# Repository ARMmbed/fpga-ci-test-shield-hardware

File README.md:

# FPGA CI Test shield - hardware design

Note: the RTL code for the FPGA lives in a separate repository: https://github.com/ARMmbed/fpga-ci-test-shield

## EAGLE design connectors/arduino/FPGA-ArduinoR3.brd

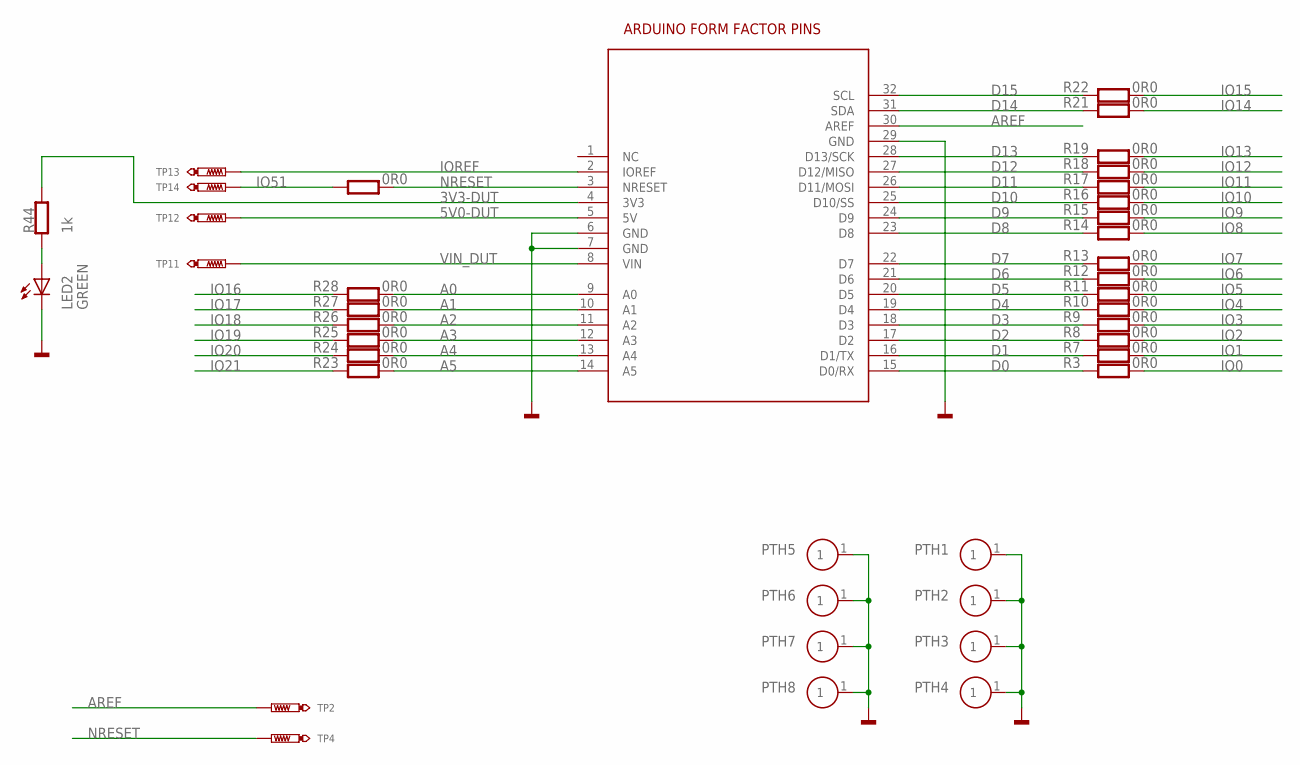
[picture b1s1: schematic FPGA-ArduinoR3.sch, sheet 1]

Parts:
BRD1: ARDUINO-R3_SILK; ARDUINO-R3-SILK
LED2: GREEN; CHIPLED_0603
PTH1, PTH2, PTH3, PTH4, PTH5, PTH6, PTH7, PTH8: FIXINGHOLE; PTH-140-300
R2, R3, R7, R8, R9, R10, R11, R12, R13, R14, R15, R16, R17, R18, R19, R21, R22, R23, R24, R25, R26, R27, R28: 0R0; 0603
R44: 1k; 0603
TP2, TP4, TP11, TP12, TP13, TP14: TEST_POINT-50R-SMD; TP50-SMD

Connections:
3V3-DUT: BRD1.4 (3V3), R44.2
5V0-DUT: BRD1.5 (5V), TP12.TP
A0: BRD1.9 (A0), R28.1
A1: BRD1.10 (A1), R27.1
A2: BRD1.11 (A2), R26.1
A3: BRD1.12 (A3), R25.1
A4: BRD1.13 (A4), R24.1
A5: BRD1.14 (A5), R23.1
AREF: BRD1.30 (AREF), TP2.TP
D0: BRD1.15 (D0/RX), R3.2
D1: BRD1.16 (D1/TX), R7.2
D2: BRD1.17 (D2), R8.2
D3: BRD1.18 (D3), R9.2
D4: BRD1.19 (D4), R10.2
D5: BRD1.20 (D5), R11.2
D6: BRD1.21 (D6), R12.2
D7: BRD1.22 (D7), R13.2
D8: BRD1.23 (D8), R14.2
D9: BRD1.24 (D9), R15.2
D10: BRD1.25 (D10/SS), R16.2
D11: BRD1.26 (D11/MOSI), R17.2
D12: BRD1.27 (D12/MISO), R18.2
D13: BRD1.28 (D13/SCK), R19.2
D14: BRD1.31 (SDA), R21.2
D15: BRD1.32 (SCL), R22.2
GND: BRD1.6 (GND), BRD1.7 (GND), BRD1.29 (GND), LED2.C, PTH1.1, PTH2.1, PTH3.1, PTH4.1, PTH5.1, PTH6.1, PTH7.1, PTH8.1; also elsewhere on the board
IO0: R3.1; also elsewhere on the board
IO1: R7.1; also elsewhere on the board
IO2: R8.1; also elsewhere on the board
IO3: R9.1; also elsewhere on the board
IO4: R10.1; also elsewhere on the board
IO5: R11.1; also elsewhere on the board
IO6: R12.1; also elsewhere on the board
IO7: R13.1; also elsewhere on the board
IO8: R14.1; also elsewhere on the board
IO9: R15.1; also elsewhere on the board
IO10: R16.1; also elsewhere on the board
IO11: R17.1; also elsewhere on the board
IO12: R18.1; also elsewhere on the board
IO13: R19.1; also elsewhere on the board
IO14: R21.1; also elsewhere on the board
IO15: R22.1; also elsewhere on the board
IO16: R28.2; also elsewhere on the board
IO17: R27.2; also elsewhere on the board
IO18: R26.2; also elsewhere on the board
IO19: R25.2; also elsewhere on the board
IO20: R24.2; also elsewhere on the board
IO21: R23.2; also elsewhere on the board
IO51: R2.2, TP14.TP; also elsewhere on the board
IOREF: BRD1.2 (IOREF), TP13.TP
unnamed: LED2.A, R44.1
NRESET: BRD1.3 (NRESET), R2.1, TP4.TP
VIN_DUT: BRD1.8 (VIN), TP11.TP

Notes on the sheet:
ARDUINO FORM FACTOR PINS

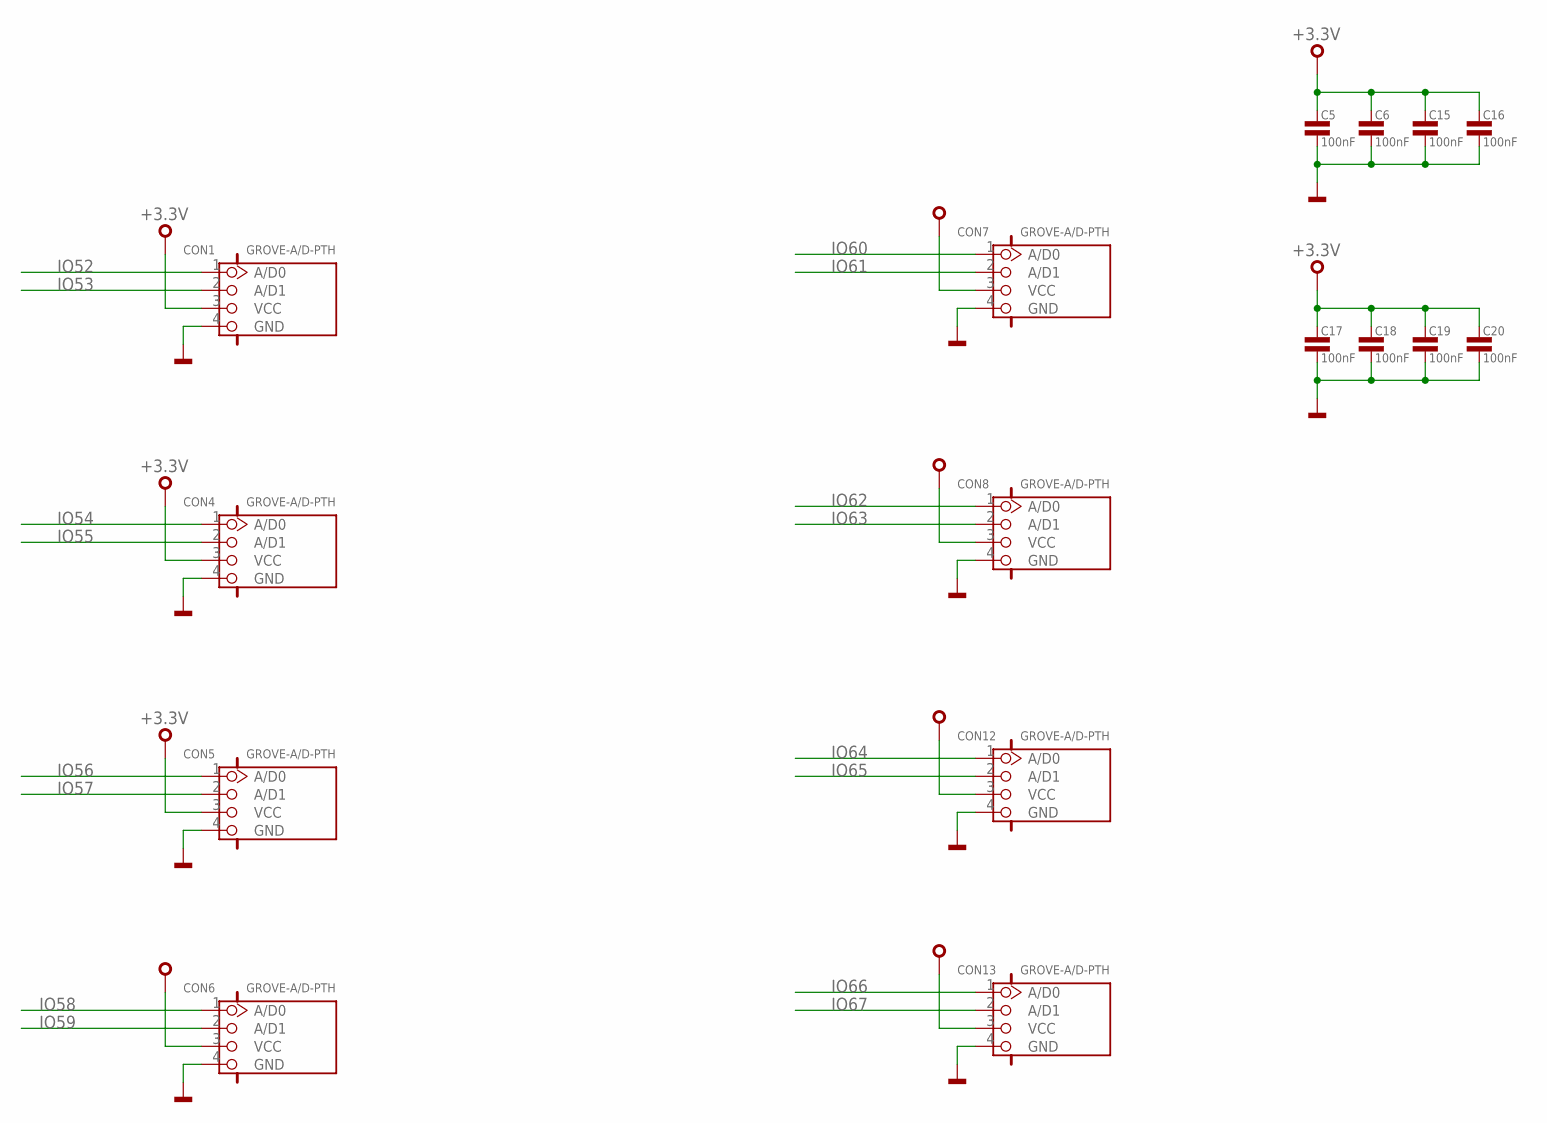
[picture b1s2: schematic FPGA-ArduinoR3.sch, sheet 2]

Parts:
C5, C6, C15, C16, C17, C18, C19, C20: 100nF; 0603
CON1, CON4, CON5, CON6, CON7, CON8, CON12, CON13: GROVE-A/D-PTH; HW4-2.0

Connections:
+3.3V: C5.1, C6.1, C15.1, C16.1, C17.1, C18.1, C19.1, C20.1, CON1.3 (VCC), CON4.3 (VCC), CON5.3 (VCC), CON6.3 (VCC), CON7.3 (VCC), CON8.3 (VCC), CON12.3 (VCC), CON13.3 (VCC); also elsewhere on the board
GND: C5.2, C6.2, C15.2, C16.2, C17.2, C18.2, C19.2, C20.2, CON1.4 (GND), CON4.4 (GND), CON5.4 (GND), CON6.4 (GND), CON7.4 (GND), CON8.4 (GND), CON12.4 (GND), CON13.4 (GND); also elsewhere on the board
IO52: CON1.1 (A/D0); also elsewhere on the board
IO53: CON1.2 (A/D1); also elsewhere on the board
IO54: CON4.1 (A/D0); also elsewhere on the board
IO55: CON4.2 (A/D1); also elsewhere on the board
IO56: CON5.1 (A/D0); also elsewhere on the board
IO57: CON5.2 (A/D1); also elsewhere on the board
IO58: CON6.1 (A/D0); also elsewhere on the board
IO59: CON6.2 (A/D1); also elsewhere on the board
IO60: CON7.1 (A/D0); also elsewhere on the board
IO61: CON7.2 (A/D1); also elsewhere on the board
IO62: CON8.1 (A/D0); also elsewhere on the board
IO63: CON8.2 (A/D1); also elsewhere on the board
IO64: CON12.1 (A/D0); also elsewhere on the board
IO65: CON12.2 (A/D1); also elsewhere on the board
IO66: CON13.1 (A/D0); also elsewhere on the board
IO67: CON13.2 (A/D1); also elsewhere on the board

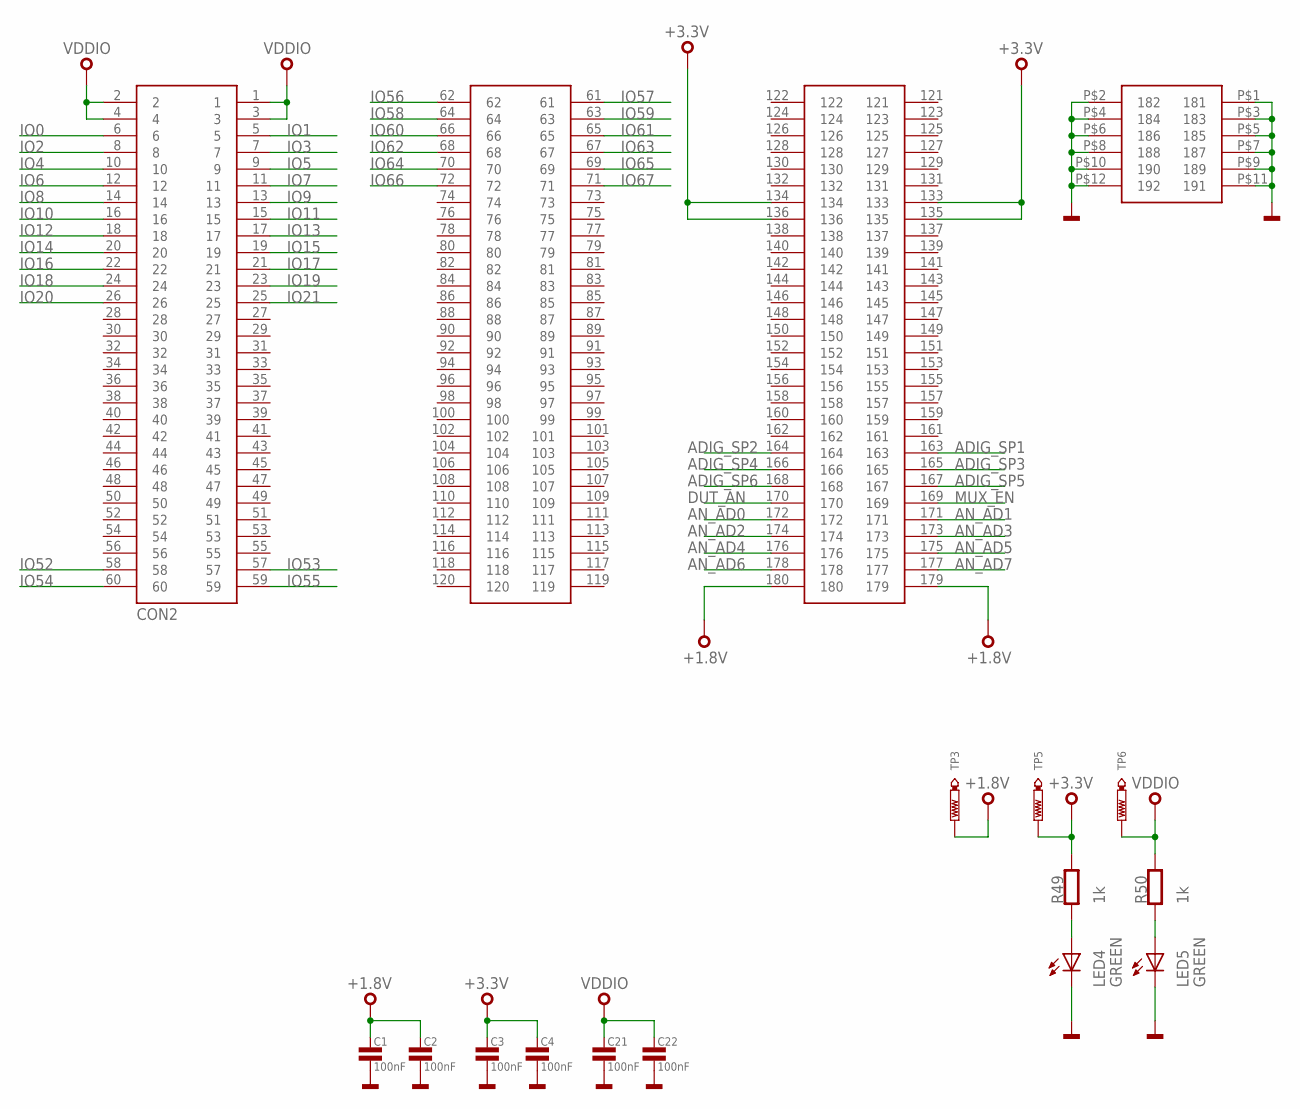
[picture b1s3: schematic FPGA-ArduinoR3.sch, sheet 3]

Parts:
C1, C2, C3, C4, C21, C22: 100nF; 0603
CON2: QSH-090-01-L-D-A
LED4, LED5: GREEN; CHIPLED_0603
R49, R50: 1k; 0603
TP3, TP5, TP6: TEST_POINT-50R-PTH; TP50-PTH

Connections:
+1.8V: C1.1, C2.1, CON2.179, CON2.180, TP3.TP; also elsewhere on the board
+3.3V: C3.1, C4.1, CON2.133, CON2.134, CON2.135, CON2.136, R49.2, TP5.TP; also elsewhere on the board
ADIG_SP1: CON2.163
ADIG_SP2: CON2.164
ADIG_SP3: CON2.165
ADIG_SP4: CON2.166
ADIG_SP5: CON2.167
ADIG_SP6: CON2.168
AN_AD0: CON2.172; also elsewhere on the board
AN_AD1: CON2.171; also elsewhere on the board
AN_AD2: CON2.174; also elsewhere on the board
AN_AD3: CON2.173; also elsewhere on the board
AN_AD4: CON2.176; also elsewhere on the board
AN_AD5: CON2.175; also elsewhere on the board
AN_AD6: CON2.178; also elsewhere on the board
AN_AD7: CON2.177; also elsewhere on the board
DUT_AN: CON2.170; also elsewhere on the board
GND: C1.2, C2.2, C3.2, C4.2, C21.2, C22.2, CON2.P$1 (181), CON2.P$2 (182), CON2.P$3 (183), CON2.P$4 (184), CON2.P$5 (185), CON2.P$6 (186), CON2.P$7 (187), CON2.P$8 (188), CON2.P$9 (189), CON2.P$10 (190), CON2.P$11 (191), CON2.P$12 (192), LED4.C, LED5.C; also elsewhere on the board
IO0: CON2.6; also elsewhere on the board
IO1: CON2.5; also elsewhere on the board
IO2: CON2.8; also elsewhere on the board
IO3: CON2.7; also elsewhere on the board
IO4: CON2.10; also elsewhere on the board
IO5: CON2.9; also elsewhere on the board
IO6: CON2.12; also elsewhere on the board
IO7: CON2.11; also elsewhere on the board
IO8: CON2.14; also elsewhere on the board
IO9: CON2.13; also elsewhere on the board
IO10: CON2.16; also elsewhere on the board
IO11: CON2.15; also elsewhere on the board
IO12: CON2.18; also elsewhere on the board
IO13: CON2.17; also elsewhere on the board
IO14: CON2.20; also elsewhere on the board
IO15: CON2.19; also elsewhere on the board
IO16: CON2.22; also elsewhere on the board
IO17: CON2.21; also elsewhere on the board
IO18: CON2.24; also elsewhere on the board
IO19: CON2.23; also elsewhere on the board
IO20: CON2.26; also elsewhere on the board
IO21: CON2.25; also elsewhere on the board
IO52: CON2.58; also elsewhere on the board
IO53: CON2.57; also elsewhere on the board
IO54: CON2.60; also elsewhere on the board
IO55: CON2.59; also elsewhere on the board
IO56: CON2.62; also elsewhere on the board
IO57: CON2.61; also elsewhere on the board
IO58: CON2.64; also elsewhere on the board
IO59: CON2.63; also elsewhere on the board
IO60: CON2.66; also elsewhere on the board
IO61: CON2.65; also elsewhere on the board
IO62: CON2.68; also elsewhere on the board
IO63: CON2.67; also elsewhere on the board
IO64: CON2.70; also elsewhere on the board
IO65: CON2.69; also elsewhere on the board
IO66: CON2.72; also elsewhere on the board
IO67: CON2.71; also elsewhere on the board
MUX_EN: CON2.169; also elsewhere on the board
unnamed: LED4.A, R49.1
unnamed: LED5.A, R50.1
VDDIO: C21.1, C22.1, CON2.1, CON2.2, CON2.3, CON2.4, R50.2, TP6.TP; also elsewhere on the board

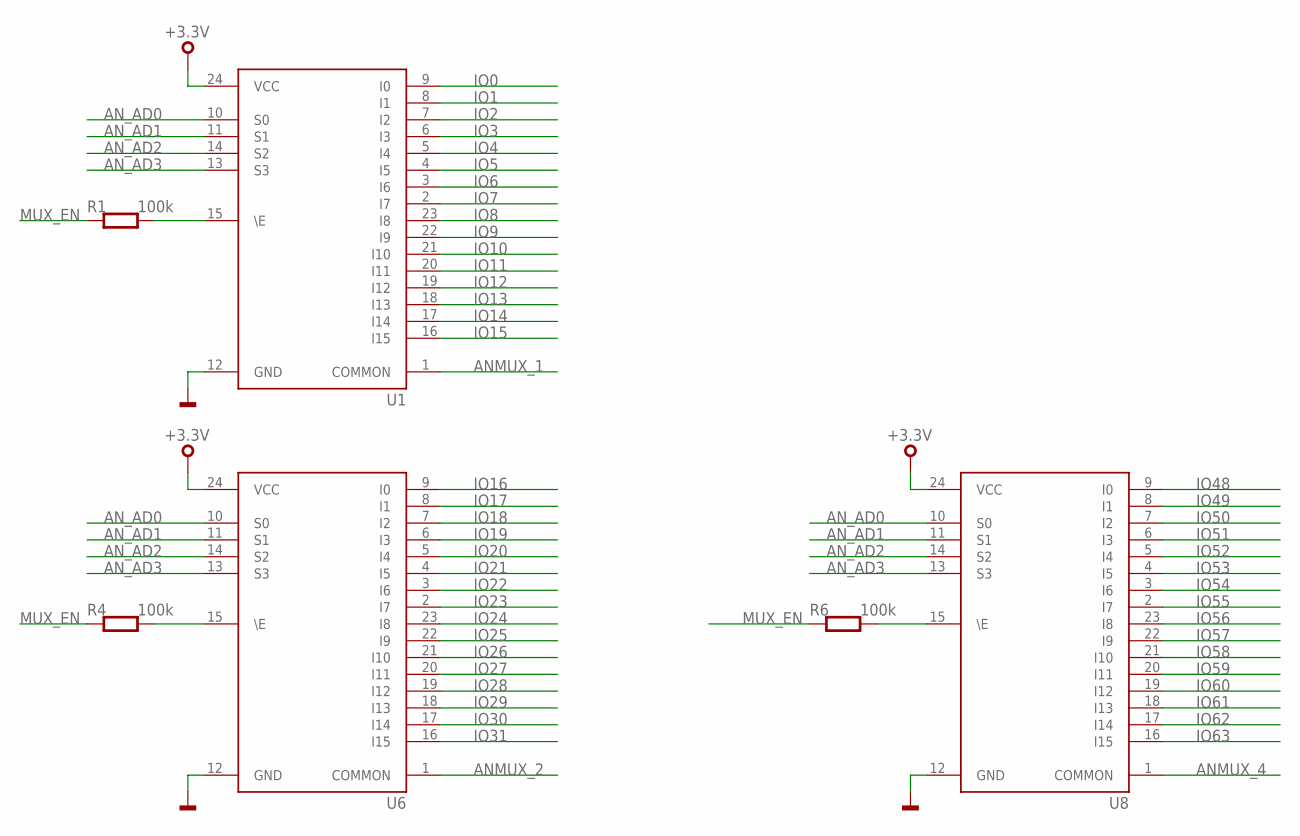
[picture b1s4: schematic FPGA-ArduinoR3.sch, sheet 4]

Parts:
R1, R4, R6: 100k; 0603
U1, U6, U8: CD74HCT4067; SO24

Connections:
+3.3V: U1.24 (VCC), U6.24 (VCC), U8.24 (VCC); also elsewhere on the board
ANMUX_1: U1.1 (COMMON); also elsewhere on the board
ANMUX_2: U6.1 (COMMON); also elsewhere on the board
ANMUX_4: U8.1 (COMMON); also elsewhere on the board
AN_AD0: U1.10 (S0), U6.10 (S0), U8.10 (S0); also elsewhere on the board
AN_AD1: U1.11 (S1), U6.11 (S1), U8.11 (S1); also elsewhere on the board
AN_AD2: U1.14 (S2), U6.14 (S2), U8.14 (S2); also elsewhere on the board
AN_AD3: U1.13 (S3), U6.13 (S3), U8.13 (S3); also elsewhere on the board
GND: U1.12 (GND), U6.12 (GND), U8.12 (GND); also elsewhere on the board
IO0: U1.9 (I0); also elsewhere on the board
IO1: U1.8 (I1); also elsewhere on the board
IO2: U1.7 (I2); also elsewhere on the board
IO3: U1.6 (I3); also elsewhere on the board
IO4: U1.5 (I4); also elsewhere on the board
IO5: U1.4 (I5); also elsewhere on the board
IO6: U1.3 (I6); also elsewhere on the board
IO7: U1.2 (I7); also elsewhere on the board
IO8: U1.23 (I8); also elsewhere on the board
IO9: U1.22 (I9); also elsewhere on the board
IO10: U1.21 (I10); also elsewhere on the board
IO11: U1.20 (I11); also elsewhere on the board
IO12: U1.19 (I12); also elsewhere on the board
IO13: U1.18 (I13); also elsewhere on the board
IO14: U1.17 (I14); also elsewhere on the board
IO15: U1.16 (I15); also elsewhere on the board
IO16: U6.9 (I0); also elsewhere on the board
IO17: U6.8 (I1); also elsewhere on the board
IO18: U6.7 (I2); also elsewhere on the board
IO19: U6.6 (I3); also elsewhere on the board
IO20: U6.5 (I4); also elsewhere on the board
IO21: U6.4 (I5); also elsewhere on the board
IO22: U6.3 (I6)
IO23: U6.2 (I7)
IO24: U6.23 (I8)
IO25: U6.22 (I9)
IO26: U6.21 (I10)
IO27: U6.20 (I11)
IO28: U6.19 (I12)
IO29: U6.18 (I13)
IO30: U6.17 (I14)
IO31: U6.16 (I15)
IO48: U8.9 (I0)
IO49: U8.8 (I1)
IO50: U8.7 (I2)
IO51: U8.6 (I3); also elsewhere on the board
IO52: U8.5 (I4); also elsewhere on the board
IO53: U8.4 (I5); also elsewhere on the board
IO54: U8.3 (I6); also elsewhere on the board
IO55: U8.2 (I7); also elsewhere on the board
IO56: U8.23 (I8); also elsewhere on the board
IO57: U8.22 (I9); also elsewhere on the board
IO58: U8.21 (I10); also elsewhere on the board
IO59: U8.20 (I11); also elsewhere on the board
IO60: U8.19 (I12); also elsewhere on the board
IO61: U8.18 (I13); also elsewhere on the board
IO62: U8.17 (I14); also elsewhere on the board
IO63: U8.16 (I15); also elsewhere on the board
MUX_EN: R1.1, R4.1, R6.1; also elsewhere on the board
unnamed: R4.2, U6.15 (\E)
unnamed: R1.2, U1.15 (\E)
unnamed: R6.2, U8.15 (\E)

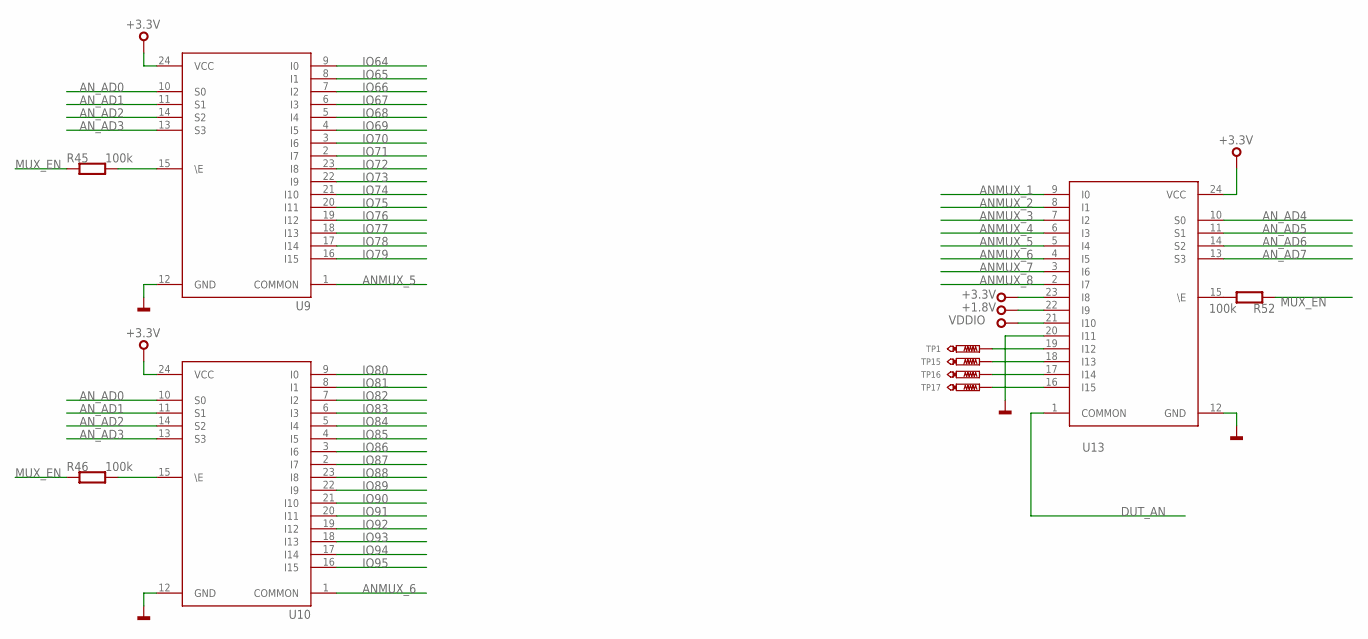
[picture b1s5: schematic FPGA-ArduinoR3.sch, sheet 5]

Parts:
R45, R46, R52: 100k; 0603
TP1, TP15, TP16, TP17: TEST_POINT-50R-PTH; TP50-PTH
U9, U10, U13: CD74HCT4067; SO24

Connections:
+1.8V: U13.22 (I9); also elsewhere on the board
+3.3V: U9.24 (VCC), U10.24 (VCC), U13.23 (I8), U13.24 (VCC); also elsewhere on the board
ANMUX_1: U13.9 (I0); also elsewhere on the board
ANMUX_2: U13.8 (I1); also elsewhere on the board
ANMUX_3: U13.7 (I2)
ANMUX_4: U13.6 (I3); also elsewhere on the board
ANMUX_5: U9.1 (COMMON), U13.5 (I4)
ANMUX_6: U10.1 (COMMON), U13.4 (I5)
ANMUX_7: U13.3 (I6)
ANMUX_8: U13.2 (I7)
AN_AD0: U9.10 (S0), U10.10 (S0); also elsewhere on the board
AN_AD1: U9.11 (S1), U10.11 (S1); also elsewhere on the board
AN_AD2: U9.14 (S2), U10.14 (S2); also elsewhere on the board
AN_AD3: U9.13 (S3), U10.13 (S3); also elsewhere on the board
AN_AD4: U13.10 (S0); also elsewhere on the board
AN_AD5: U13.11 (S1); also elsewhere on the board
AN_AD6: U13.14 (S2); also elsewhere on the board
AN_AD7: U13.13 (S3); also elsewhere on the board
DUT_AN: U13.1 (COMMON); also elsewhere on the board
GND: U9.12 (GND), U10.12 (GND), U13.12 (GND), U13.20 (I11); also elsewhere on the board
IO64: U9.9 (I0); also elsewhere on the board
IO65: U9.8 (I1); also elsewhere on the board
IO66: U9.7 (I2); also elsewhere on the board
IO67: U9.6 (I3); also elsewhere on the board
IO68: U9.5 (I4)
IO69: U9.4 (I5)
IO70: U9.3 (I6)
IO71: U9.2 (I7)
IO72: U9.23 (I8)
IO73: U9.22 (I9)
IO74: U9.21 (I10)
IO75: U9.20 (I11)
IO76: U9.19 (I12)
IO77: U9.18 (I13)
IO78: U9.17 (I14)
IO79: U9.16 (I15)
IO80: U10.9 (I0)
IO81: U10.8 (I1)
IO82: U10.7 (I2)
IO83: U10.6 (I3)
IO84: U10.5 (I4)
IO85: U10.4 (I5)
IO86: U10.3 (I6)
IO87: U10.2 (I7)
IO88: U10.23 (I8)
IO89: U10.22 (I9)
IO90: U10.21 (I10)
IO91: U10.20 (I11)
IO92: U10.19 (I12)
IO93: U10.18 (I13)
IO94: U10.17 (I14)
IO95: U10.16 (I15)
MUX_EN: R45.1, R46.1, R52.1; also elsewhere on the board
unnamed: R45.2, U9.15 (\E)
unnamed: R46.2, U10.15 (\E)
unnamed: R52.2, U13.15 (\E)
unnamed: TP1.TP, U13.19 (I12)
unnamed: TP15.TP, U13.18 (I13)
unnamed: TP16.TP, U13.17 (I14)
unnamed: TP17.TP, U13.16 (I15)
VDDIO: U13.21 (I10); also elsewhere on the board

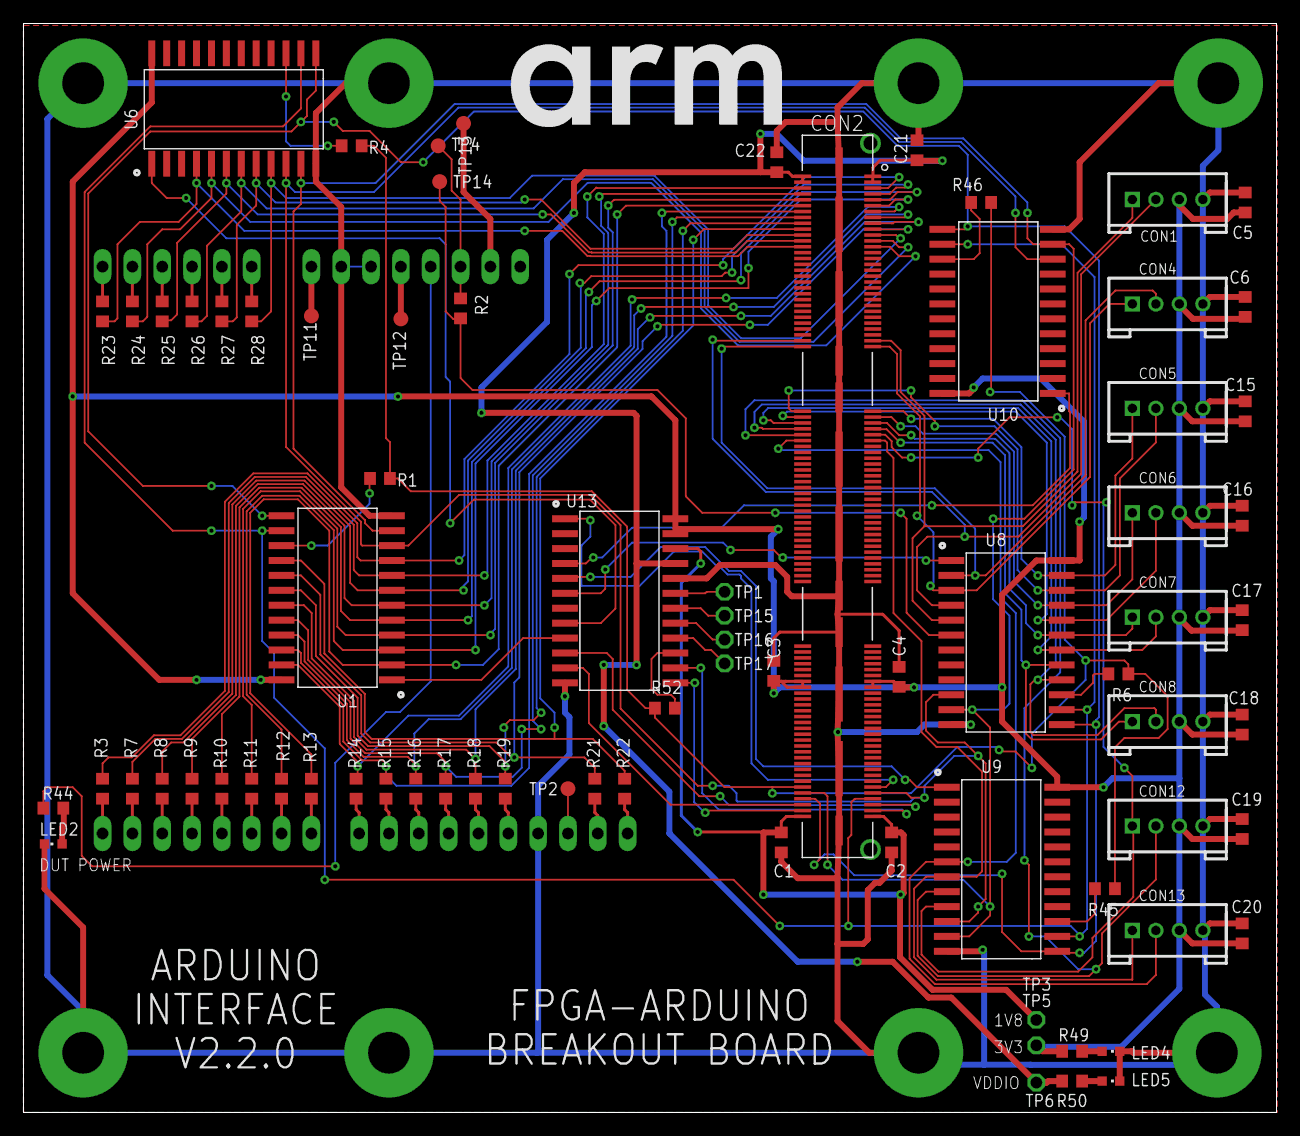
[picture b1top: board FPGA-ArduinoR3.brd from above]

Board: 2 copper layers, 106.7 x 92.7 mm, 86 parts (0 on the bottom side), 99 nets.

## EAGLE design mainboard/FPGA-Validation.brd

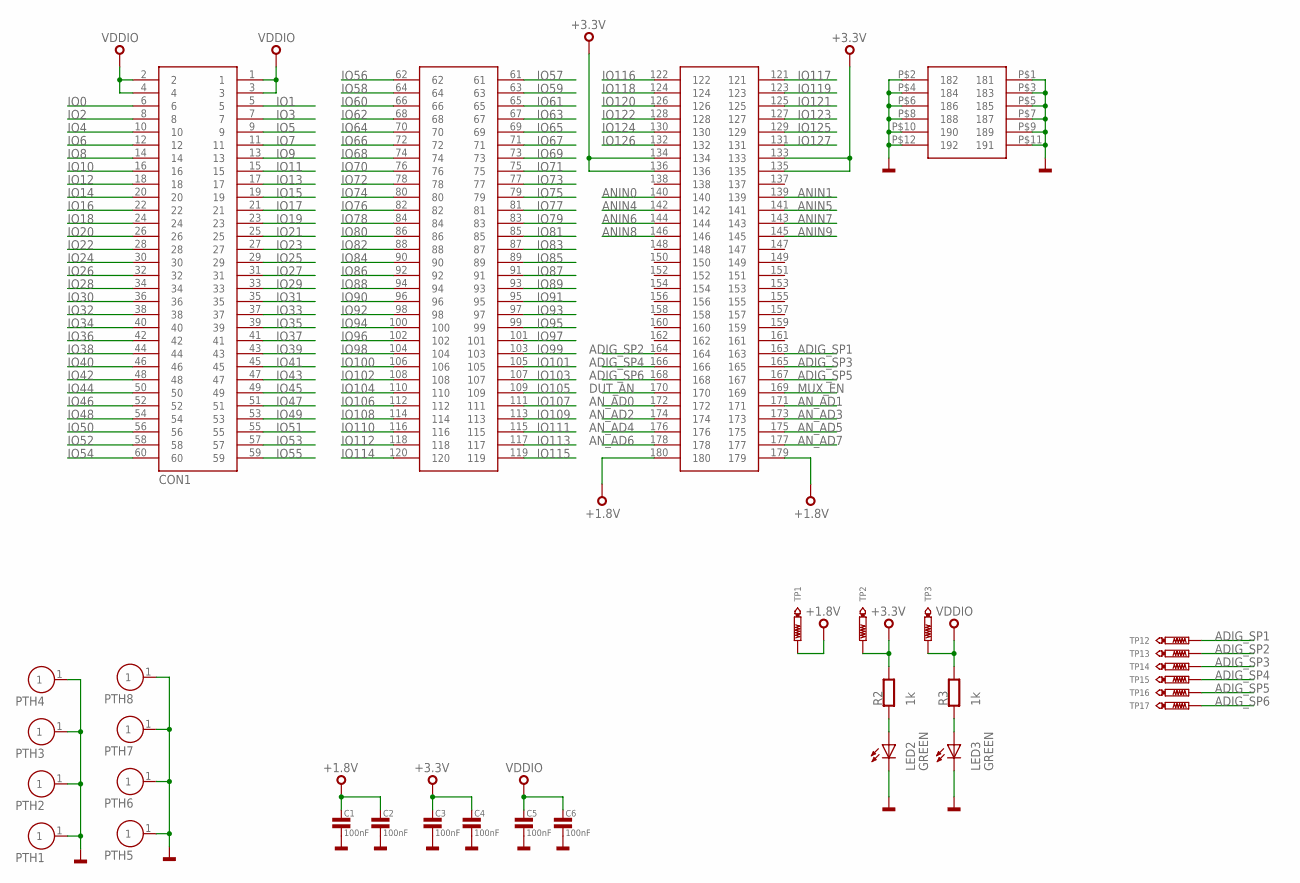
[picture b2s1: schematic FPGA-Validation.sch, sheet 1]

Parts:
C1, C2, C3, C4, C5, C6: 100nF; 0603
CON1: QSH-090-01-L-D-A
LED2, LED3: GREEN; CHIPLED_0603
PTH1, PTH2, PTH3, PTH4, PTH5, PTH6, PTH7, PTH8: FIXINGHOLE; PTH-140-300
R2, R3: 1k; 0603
TP1, TP2, TP3: TEST_POINT-50R-PTH; TP50-PTH
TP12, TP13, TP14, TP15, TP16, TP17: TEST_POINT-25R-SMD; TP25-SMD

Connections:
+1.8V: C1.1, C2.1, CON1.179, CON1.180, TP1.TP; also elsewhere on the board
+3.3V: C3.1, C4.1, CON1.133, CON1.134, CON1.135, CON1.136, R2.2, TP2.TP; also elsewhere on the board
ADIG_SP1: CON1.163, TP12.TP
ADIG_SP2: CON1.164, TP13.TP
ADIG_SP3: CON1.165, TP14.TP
ADIG_SP4: CON1.166, TP15.TP
ADIG_SP5: CON1.167, TP16.TP
ADIG_SP6: CON1.168, TP17.TP
ANIN0: CON1.140; also elsewhere on the board
ANIN1: CON1.139; also elsewhere on the board
ANIN4: CON1.142; also elsewhere on the board
ANIN5: CON1.141; also elsewhere on the board
ANIN6: CON1.144; also elsewhere on the board
ANIN7: CON1.143; also elsewhere on the board
ANIN8: CON1.146; also elsewhere on the board
ANIN9: CON1.145; also elsewhere on the board
AN_AD0: CON1.172; also elsewhere on the board
AN_AD1: CON1.171; also elsewhere on the board
AN_AD2: CON1.174; also elsewhere on the board
AN_AD3: CON1.173; also elsewhere on the board
AN_AD4: CON1.176; also elsewhere on the board
AN_AD5: CON1.175; also elsewhere on the board
AN_AD6: CON1.178; also elsewhere on the board
AN_AD7: CON1.177; also elsewhere on the board
DUT_AN: CON1.170; also elsewhere on the board
GND: C1.2, C2.2, C3.2, C4.2, C5.2, C6.2, CON1.P$1 (181), CON1.P$2 (182), CON1.P$3 (183), CON1.P$4 (184), CON1.P$5 (185), CON1.P$6 (186), CON1.P$7 (187), CON1.P$8 (188), CON1.P$9 (189), CON1.P$10 (190), CON1.P$11 (191), CON1.P$12 (192), LED2.C, LED3.C, PTH1.1, PTH2.1, PTH3.1, PTH4.1, PTH5.1, PTH6.1, PTH7.1, PTH8.1; also elsewhere on the board
IO0: CON1.6; also elsewhere on the board
IO1: CON1.5; also elsewhere on the board
IO2: CON1.8; also elsewhere on the board
IO3: CON1.7; also elsewhere on the board
IO4: CON1.10; also elsewhere on the board
IO5: CON1.9; also elsewhere on the board
IO6: CON1.12; also elsewhere on the board
IO7: CON1.11; also elsewhere on the board
IO8: CON1.14; also elsewhere on the board
IO9: CON1.13; also elsewhere on the board
IO10: CON1.16; also elsewhere on the board
IO11: CON1.15; also elsewhere on the board
IO12: CON1.18; also elsewhere on the board
IO13: CON1.17; also elsewhere on the board
IO14: CON1.20; also elsewhere on the board
IO15: CON1.19; also elsewhere on the board
IO16: CON1.22; also elsewhere on the board
IO17: CON1.21; also elsewhere on the board
IO18: CON1.24; also elsewhere on the board
IO19: CON1.23; also elsewhere on the board
IO20: CON1.26; also elsewhere on the board
IO21: CON1.25; also elsewhere on the board
IO22: CON1.28; also elsewhere on the board
IO23: CON1.27; also elsewhere on the board
IO24: CON1.30; also elsewhere on the board
IO25: CON1.29; also elsewhere on the board
IO26: CON1.32; also elsewhere on the board
IO27: CON1.31; also elsewhere on the board
IO28: CON1.34; also elsewhere on the board
IO29: CON1.33; also elsewhere on the board
IO30: CON1.36; also elsewhere on the board
IO31: CON1.35; also elsewhere on the board
IO32: CON1.38; also elsewhere on the board
IO33: CON1.37; also elsewhere on the board
IO34: CON1.40; also elsewhere on the board
IO35: CON1.39; also elsewhere on the board
IO36: CON1.42; also elsewhere on the board
IO37: CON1.41; also elsewhere on the board
IO38: CON1.44; also elsewhere on the board
IO39: CON1.43; also elsewhere on the board
IO40: CON1.46; also elsewhere on the board
IO41: CON1.45; also elsewhere on the board
IO42: CON1.48; also elsewhere on the board
IO43: CON1.47; also elsewhere on the board
IO44: CON1.50; also elsewhere on the board
IO45: CON1.49; also elsewhere on the board
IO46: CON1.52; also elsewhere on the board
IO47: CON1.51; also elsewhere on the board
IO48: CON1.54; also elsewhere on the board
IO49: CON1.53; also elsewhere on the board
IO50: CON1.56; also elsewhere on the board
IO51: CON1.55; also elsewhere on the board
IO52: CON1.58; also elsewhere on the board
IO53: CON1.57; also elsewhere on the board
IO54: CON1.60; also elsewhere on the board
IO55: CON1.59; also elsewhere on the board
IO56: CON1.62; also elsewhere on the board
IO57: CON1.61; also elsewhere on the board
IO58: CON1.64; also elsewhere on the board
IO59: CON1.63; also elsewhere on the board
IO60: CON1.66; also elsewhere on the board
IO61: CON1.65; also elsewhere on the board
IO62: CON1.68; also elsewhere on the board
IO63: CON1.67; also elsewhere on the board
IO64: CON1.70; also elsewhere on the board
IO65: CON1.69; also elsewhere on the board
IO66: CON1.72; also elsewhere on the board
IO67: CON1.71; also elsewhere on the board
IO68: CON1.74; also elsewhere on the board
IO69: CON1.73; also elsewhere on the board
IO70: CON1.76; also elsewhere on the board
IO71: CON1.75; also elsewhere on the board
IO72: CON1.78; also elsewhere on the board
IO73: CON1.77; also elsewhere on the board
IO74: CON1.80; also elsewhere on the board
IO75: CON1.79; also elsewhere on the board
IO76: CON1.82; also elsewhere on the board
IO77: CON1.81; also elsewhere on the board
IO78: CON1.84; also elsewhere on the board
IO79: CON1.83; also elsewhere on the board
IO80: CON1.86; also elsewhere on the board
IO81: CON1.85; also elsewhere on the board
IO82: CON1.88; also elsewhere on the board
IO83: CON1.87; also elsewhere on the board
IO84: CON1.90; also elsewhere on the board
IO85: CON1.89; also elsewhere on the board
IO86: CON1.92; also elsewhere on the board
IO87: CON1.91; also elsewhere on the board
IO88: CON1.94; also elsewhere on the board
IO89: CON1.93; also elsewhere on the board
IO90: CON1.96; also elsewhere on the board
IO91: CON1.95; also elsewhere on the board
IO92: CON1.98; also elsewhere on the board
IO93: CON1.97; also elsewhere on the board
IO94: CON1.100; also elsewhere on the board
IO95: CON1.99; also elsewhere on the board
IO96: CON1.102; also elsewhere on the board
IO97: CON1.101; also elsewhere on the board
IO98: CON1.104; also elsewhere on the board
IO99: CON1.103; also elsewhere on the board
IO100: CON1.106; also elsewhere on the board
IO101: CON1.105; also elsewhere on the board
IO102: CON1.108; also elsewhere on the board
IO103: CON1.107; also elsewhere on the board
IO104: CON1.110; also elsewhere on the board
IO105: CON1.109; also elsewhere on the board
IO106: CON1.112; also elsewhere on the board
IO107: CON1.111; also elsewhere on the board
IO108: CON1.114; also elsewhere on the board
IO109: CON1.113; also elsewhere on the board
IO110: CON1.116; also elsewhere on the board
IO111: CON1.115; also elsewhere on the board
IO112: CON1.118; also elsewhere on the board
IO113: CON1.117; also elsewhere on the board
IO114: CON1.120; also elsewhere on the board
IO115: CON1.119; also elsewhere on the board
IO116: CON1.122; also elsewhere on the board
IO117: CON1.121; also elsewhere on the board
IO118: CON1.124; also elsewhere on the board
IO119: CON1.123; also elsewhere on the board
IO120: CON1.126; also elsewhere on the board
IO121: CON1.125; also elsewhere on the board
IO122: CON1.128; also elsewhere on the board
IO123: CON1.127; also elsewhere on the board
IO124: CON1.130; also elsewhere on the board
IO125: CON1.129; also elsewhere on the board
IO126: CON1.132; also elsewhere on the board
IO127: CON1.131; also elsewhere on the board
MUX_EN: CON1.169; also elsewhere on the board
unnamed: LED3.A, R3.1
unnamed: LED2.A, R2.1
VDDIO: C5.1, C6.1, CON1.1, CON1.2, CON1.3, CON1.4, R3.2, TP3.TP; also elsewhere on the board
